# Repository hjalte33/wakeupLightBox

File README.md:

# Main Objectives
* dimable light - optionally colored to add natual lighting effects
* speaker to play music/radio
* screen showing the time and to provide a simple interface
* buttons to make main settings
* alarm interface to set alarm settings
* Wifi connectivity
* simple webinterface

# Nice to have
* Temperature + humidity sensor (BME280)
* Fan to circulate air around in your room
* Big LCD/LED matrix display for showing the time
* weather information 
* google assistent
* Bluetooth speaker functionality

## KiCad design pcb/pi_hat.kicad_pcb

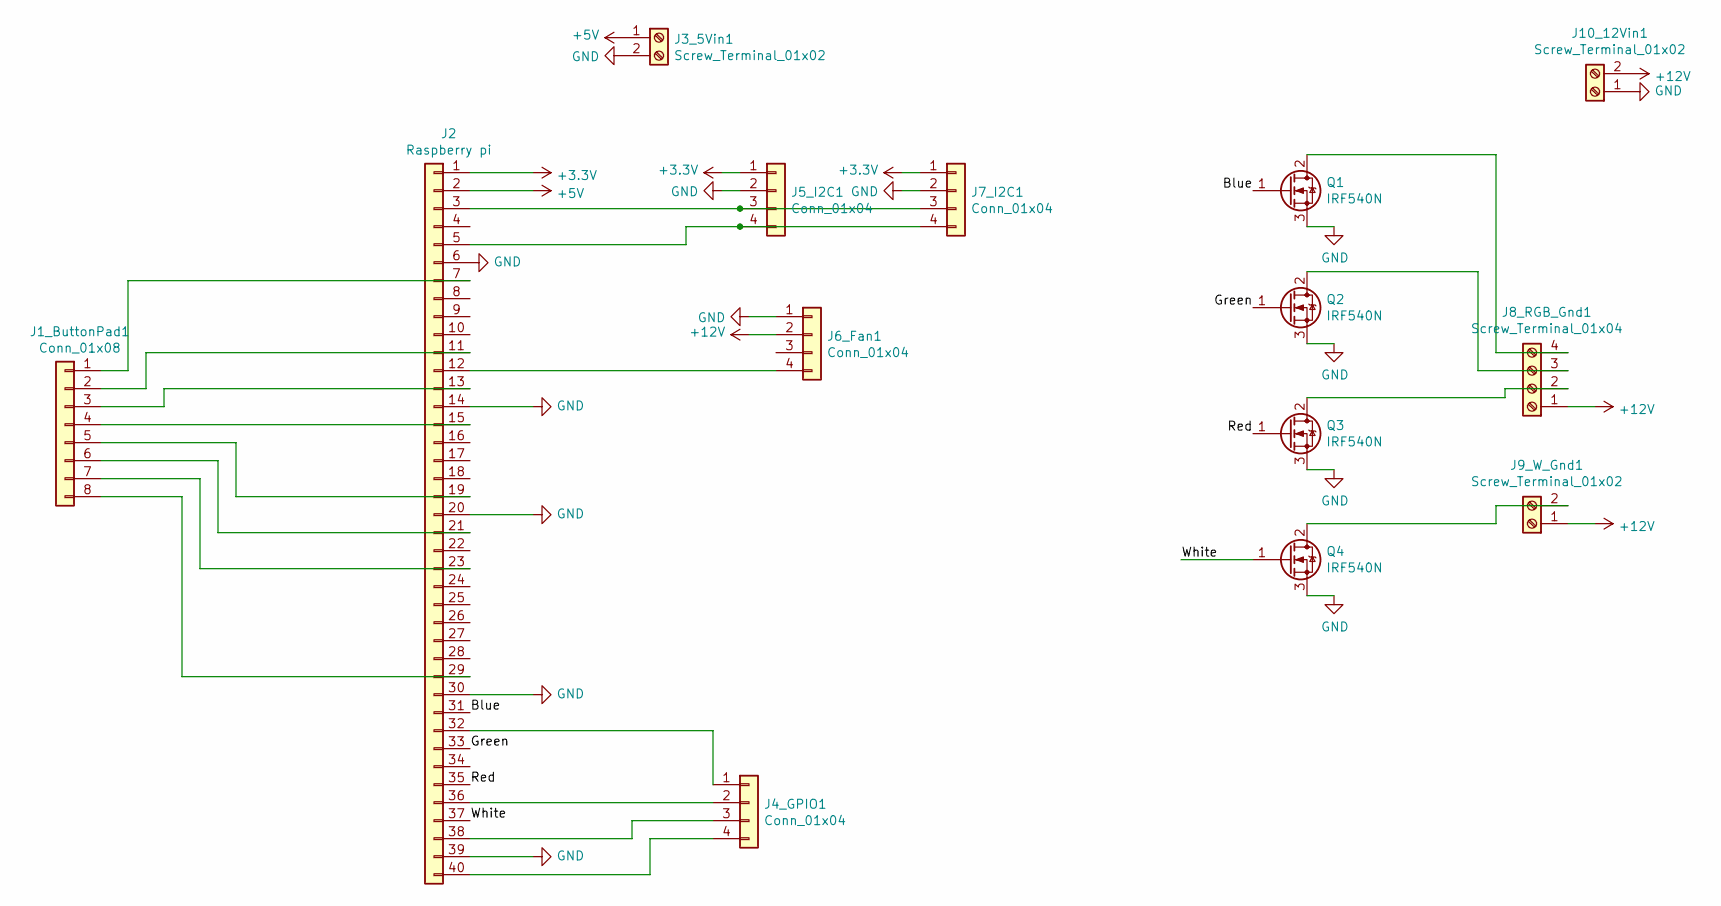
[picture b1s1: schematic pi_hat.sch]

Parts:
J1_ButtonPad1: Conn_01x08; PinSocket_1x08_P2.54mm_Vertical
J2: Raspberry pi; PinSocket_2x20_P2.54mm_Vertical
J3_5Vin1, J9_W_Gnd1, J10_12Vin1: Screw_Terminal_01x02; TerminalBlock_bornier-2_P5.08mm
J4_GPIO1, J5_I2C1, J6_Fan1, J7_I2C1: Conn_01x04; PinHeader_1x04_P2.54mm_Vertical
J8_RGB_Gnd1: Screw_Terminal_01x04; TerminalBlock_bornier-4_P5.08mm
Q1, Q2, Q3, Q4: IRF540N; TO-220-3_Vertical

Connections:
+3V3: J2.1, J5_I2C1.1, J7_I2C1.1
+5V: J2.2, J3_5Vin1.1
+12V: J6_Fan1.2, J8_RGB_Gnd1.1, J9_W_Gnd1.1, J10_12Vin1.2
/Blue: J2.31, Q1.1 (G)
/Green: J2.33, Q2.1 (G)
/Red: J2.35, Q3.1 (G)
/White: J2.37, Q4.1 (G)
GND: J2.6, J2.14, J2.20, J2.30, J2.39, J3_5Vin1.2, J5_I2C1.2, J6_Fan1.1, J7_I2C1.2, J10_12Vin1.1, Q1.3 (S), Q2.3 (S), Q3.3 (S), Q4.3 (S)
unnamed: J1_ButtonPad1.1, J2.7
unnamed: J1_ButtonPad1.2, J2.11
unnamed: J1_ButtonPad1.3, J2.13
unnamed: J1_ButtonPad1.4, J2.15
unnamed: J1_ButtonPad1.5, J2.19
unnamed: J1_ButtonPad1.6, J2.21
unnamed: J1_ButtonPad1.7, J2.23
unnamed: J1_ButtonPad1.8, J2.29
unnamed: J2.3, J5_I2C1.3, J7_I2C1.3
unnamed: J2.5, J5_I2C1.4, J7_I2C1.4
unnamed: J2.12, J6_Fan1.4
unnamed: J2.32, J4_GPIO1.1
unnamed: J2.36, J4_GPIO1.2
unnamed: J2.38, J4_GPIO1.3
unnamed: J2.40, J4_GPIO1.4
unnamed: J8_RGB_Gnd1.2, Q3.2 (D)
unnamed: J8_RGB_Gnd1.3, Q2.2 (D)
unnamed: J8_RGB_Gnd1.4, Q1.2 (D)
unnamed: J9_W_Gnd1.2, Q4.2 (D)

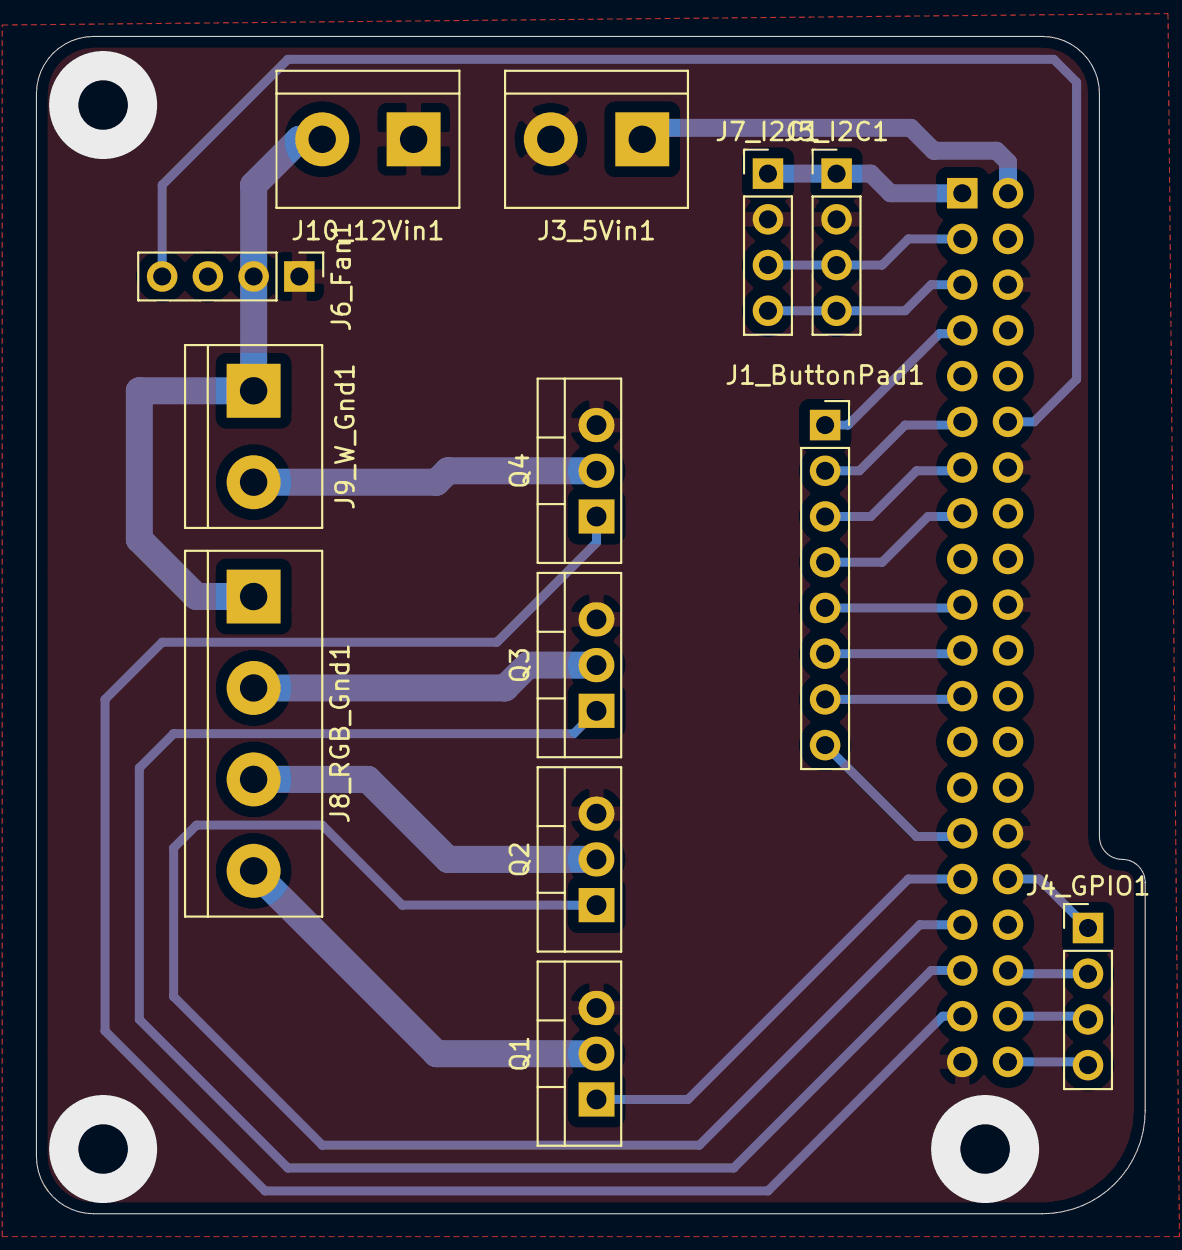
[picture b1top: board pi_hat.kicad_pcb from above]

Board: 2 copper layers, 61.6 x 65.4 mm, 14 parts (1 on the bottom side), 27 nets.

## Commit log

2020-11-21 Squashed 'cad/laserlib/' content from commit e757645
    git-subtree-dir: cad/laserlib
    git-subtree-split: e7576457ef733fbe2f45854270c4164f2d596b5d
2020-11-21 folder rename
2020-11-22 new lib: laserlib
2020-11-22 Squashed 'cad/laserlib/' changes from e757645..39ecd86
    39ecd86 bugfix:inverse fingers had wrong kerf
    git-subtree-dir: cad/laserlib
    git-subtree-split: 39ecd86c746166f8a9c9e66e1bbbc6cbe3f1c35a
2020-11-27 bugfixes + new features + design changes
2020-11-27 lot of new things added.
2020-11-30 buttonpad and feet
2020-11-30 first draft
2020-12-03 pcb v1
2020-12-04 minor changes. v1 done
2020-12-09 add: parts list
2020-12-09 add: buttons and wire hole for mains power
2020-12-30 adding outside kerf to llCutout
2020-12-30 kerf and clip test
2020-12-30 fix: kerf on clips
2020-12-30 minor design changes
2020-12-30 Squashed 'cad/laserlib/' changes from 39ecd86..55e65c8
    55e65c8 Created README - first draft
    eca89cb bugfixes + new features + design changes
    git-subtree-dir: cad/laserlib
    git-subtree-split: 55e65c83d6f4c7274254629d7d7cb9a819eadea6
2021-01-21 final tweaks
